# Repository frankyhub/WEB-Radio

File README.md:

<div align="center">

|[:skull:ISSUE](https://github.com/frankyhub/WEB-Radio/issues?q=is%3Aissue)|[:speech_balloon: Forum /Discussion](https://github.com/frankyhub/WEB-Radio/discussions)|[:grey_question:WiKi](https://github.com/frankyhub/WEB-Radio/wiki)||
|--|--|--|--|
| | | | |
<a href="https://github.com/frankyhub/WEB-Radio/issues">|<a href="https://github.com/frankyhub/WEB-Radio/discussions">|<a href="https://github.com/frankyhub/WEB-Radio/6eleases">||
|| <a href="https://github.com/frankyhub/WEB-Radio/pulse" alt="Activity">| <a href="https://github.com/frankyhub/WEB-Radio/graphs/traffic">  |<a href="https://github.com/frankyhub?tab=stars"> ||

<br> <br>

</div>

# Story

Dieses Repository beinhaltet die Dateien eines WEB Radios. Über einen Drehgeber Encoder sind 20 Radiostationen wählbar. Die Lautstärke wird direkt über das Poti am Audio-Verstärker eingestellt. Das LCD-Display zeigt die gewählte Radio-Station an. Die Radio-Stationen sind über einen WEB-Server abruf- und veränderbar.<br>
Nach dem Einschalten über den Volume-Regler/Schalter, sucht der Mikrocontroller nach einer gültigen WLAN-Verbindung und stellt die zuletzt gewählte Radio-Station ein. Liegt keine gültige WLAN-Verbindung vor, startet der WLAN-Manager. Über die Netzwerkeinstellung des Handys/Tablet kann nach der Auswahl „WEBRADIO“ der WLAN-Manager mit der IP-Adresse 192.168.4.1 aufgerufen werden. Über den WLAN-Manager sind die eigenen WLAN-Zugangsdaten speicherbar. Nach dem speichern der Zugangsdaten startet der Mikrocontroller neu und das LCD-Display zeigt die IP-Adresse des WEB-Servers und danach die gewählte Radio-Station an.

WEB-Radio WiFi-Einstellung

<br> <br>

<br> <br>

WEB-Radio LCD Display

<br> <br>

<br> <br>

WEB-Radio WEB-Server Senderliste

<br> <br>

WEB-Radio Verdrahtung

<br> <br>

---

<div style="position:absolute; left:2cm; ">   
<ol class="breadcrumb" style="border-top: 2px solid black;border-bottom:2px solid black; height: 45px; width: 900px;"> <p align="center"><a href="#oben">nach oben</a></p></ol>
</div>  

---

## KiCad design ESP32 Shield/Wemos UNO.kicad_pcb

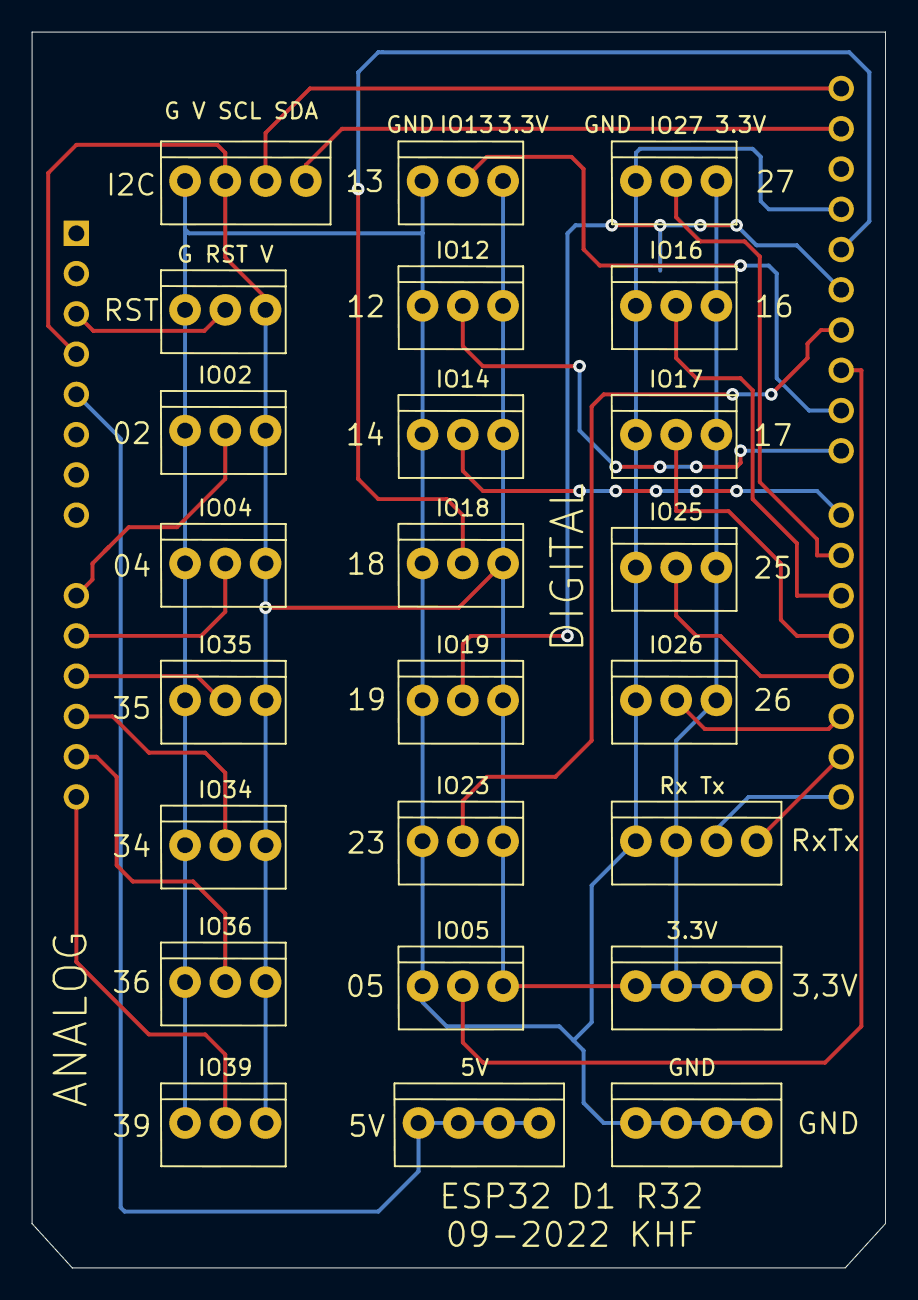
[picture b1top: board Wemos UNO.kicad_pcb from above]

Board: 2 copper layers, 53.8 x 78.0 mm, 25 parts (1 on the bottom side), 26 nets.

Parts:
3.3V, 5V: PL-Stecker_4pol_Data; PL-Stecker
A1: Arduino_UNO_R3
G RST V: PL-Stecker_3pol; PL-Stecker3pol
G V SCL SDA: PL-Stecker_4pol_I2C; PL-Stecker
GND: PL-Stecker_4pol_Data; PL-Stecker
IO02, IO04, IO05, IO12, IO13, IO14, IO16, IO17, IO18, IO19, IO23, IO25, IO26, IO27, IO34, IO35, IO36, IO39: PL-Stecker_3pol; PL-Stecker3pol
Rx Tx: PL-Stecker_4pol_I2C; PL-Stecker

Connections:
unnamed: A1.3, G RST V.2
unnamed: 3.3V.1, 3.3V.2, 3.3V.3, 3.3V.4, A1.4, G RST V.3, G V SCL SDA.2, IO02.3, IO04.3, IO05.3, IO12.3, IO13.3, IO14.3, IO16.3, IO17.3, IO18.3, IO19.3, IO23.3, IO25.3, IO26.3, IO27.3, IO34.3, IO35.3, IO36.3, IO39.3, Rx Tx.2
unnamed: 5V.1, 5V.2, 5V.3, 5V.4, A1.5
unnamed: A1.9, IO02.2
unnamed: A1.10, IO04.2
unnamed: A1.11, IO35.2
unnamed: A1.12, IO34.2
unnamed: A1.13, IO36.2
unnamed: A1.14, IO39.2
unnamed: A1.15, Rx Tx.3
unnamed: A1.16, Rx Tx.4
unnamed: A1.17, IO26.2
unnamed: A1.18, IO25.2
unnamed: A1.19, IO17.2
unnamed: A1.20, IO16.2
unnamed: A1.21, IO27.2
unnamed: A1.22, IO14.2
unnamed: A1.23, IO12.2
unnamed: A1.24, IO13.2
unnamed: A1.25, IO05.2
unnamed: A1.26, IO23.2
unnamed: A1.27, IO19.2
unnamed: A1.28, IO18.2
unnamed: A1.29, G RST V.1, G V SCL SDA.1, GND.1, GND.2, GND.3, GND.4, IO02.1, IO04.1, IO05.1, IO12.1, IO13.1, IO14.1, IO16.1, IO17.1, IO18.1, IO19.1, IO23.1, IO25.1, IO26.1, IO27.1, IO34.1, IO35.1, IO36.1, IO39.1, Rx Tx.1
unnamed: A1.31, G V SCL SDA.4
unnamed: A1.32, G V SCL SDA.3

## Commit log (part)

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2024-01-27 Pfad README.md
2024-06-19 V 19.06.2024
2024-10-12 V12102024
